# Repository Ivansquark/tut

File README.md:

Some examples for future fast remembering

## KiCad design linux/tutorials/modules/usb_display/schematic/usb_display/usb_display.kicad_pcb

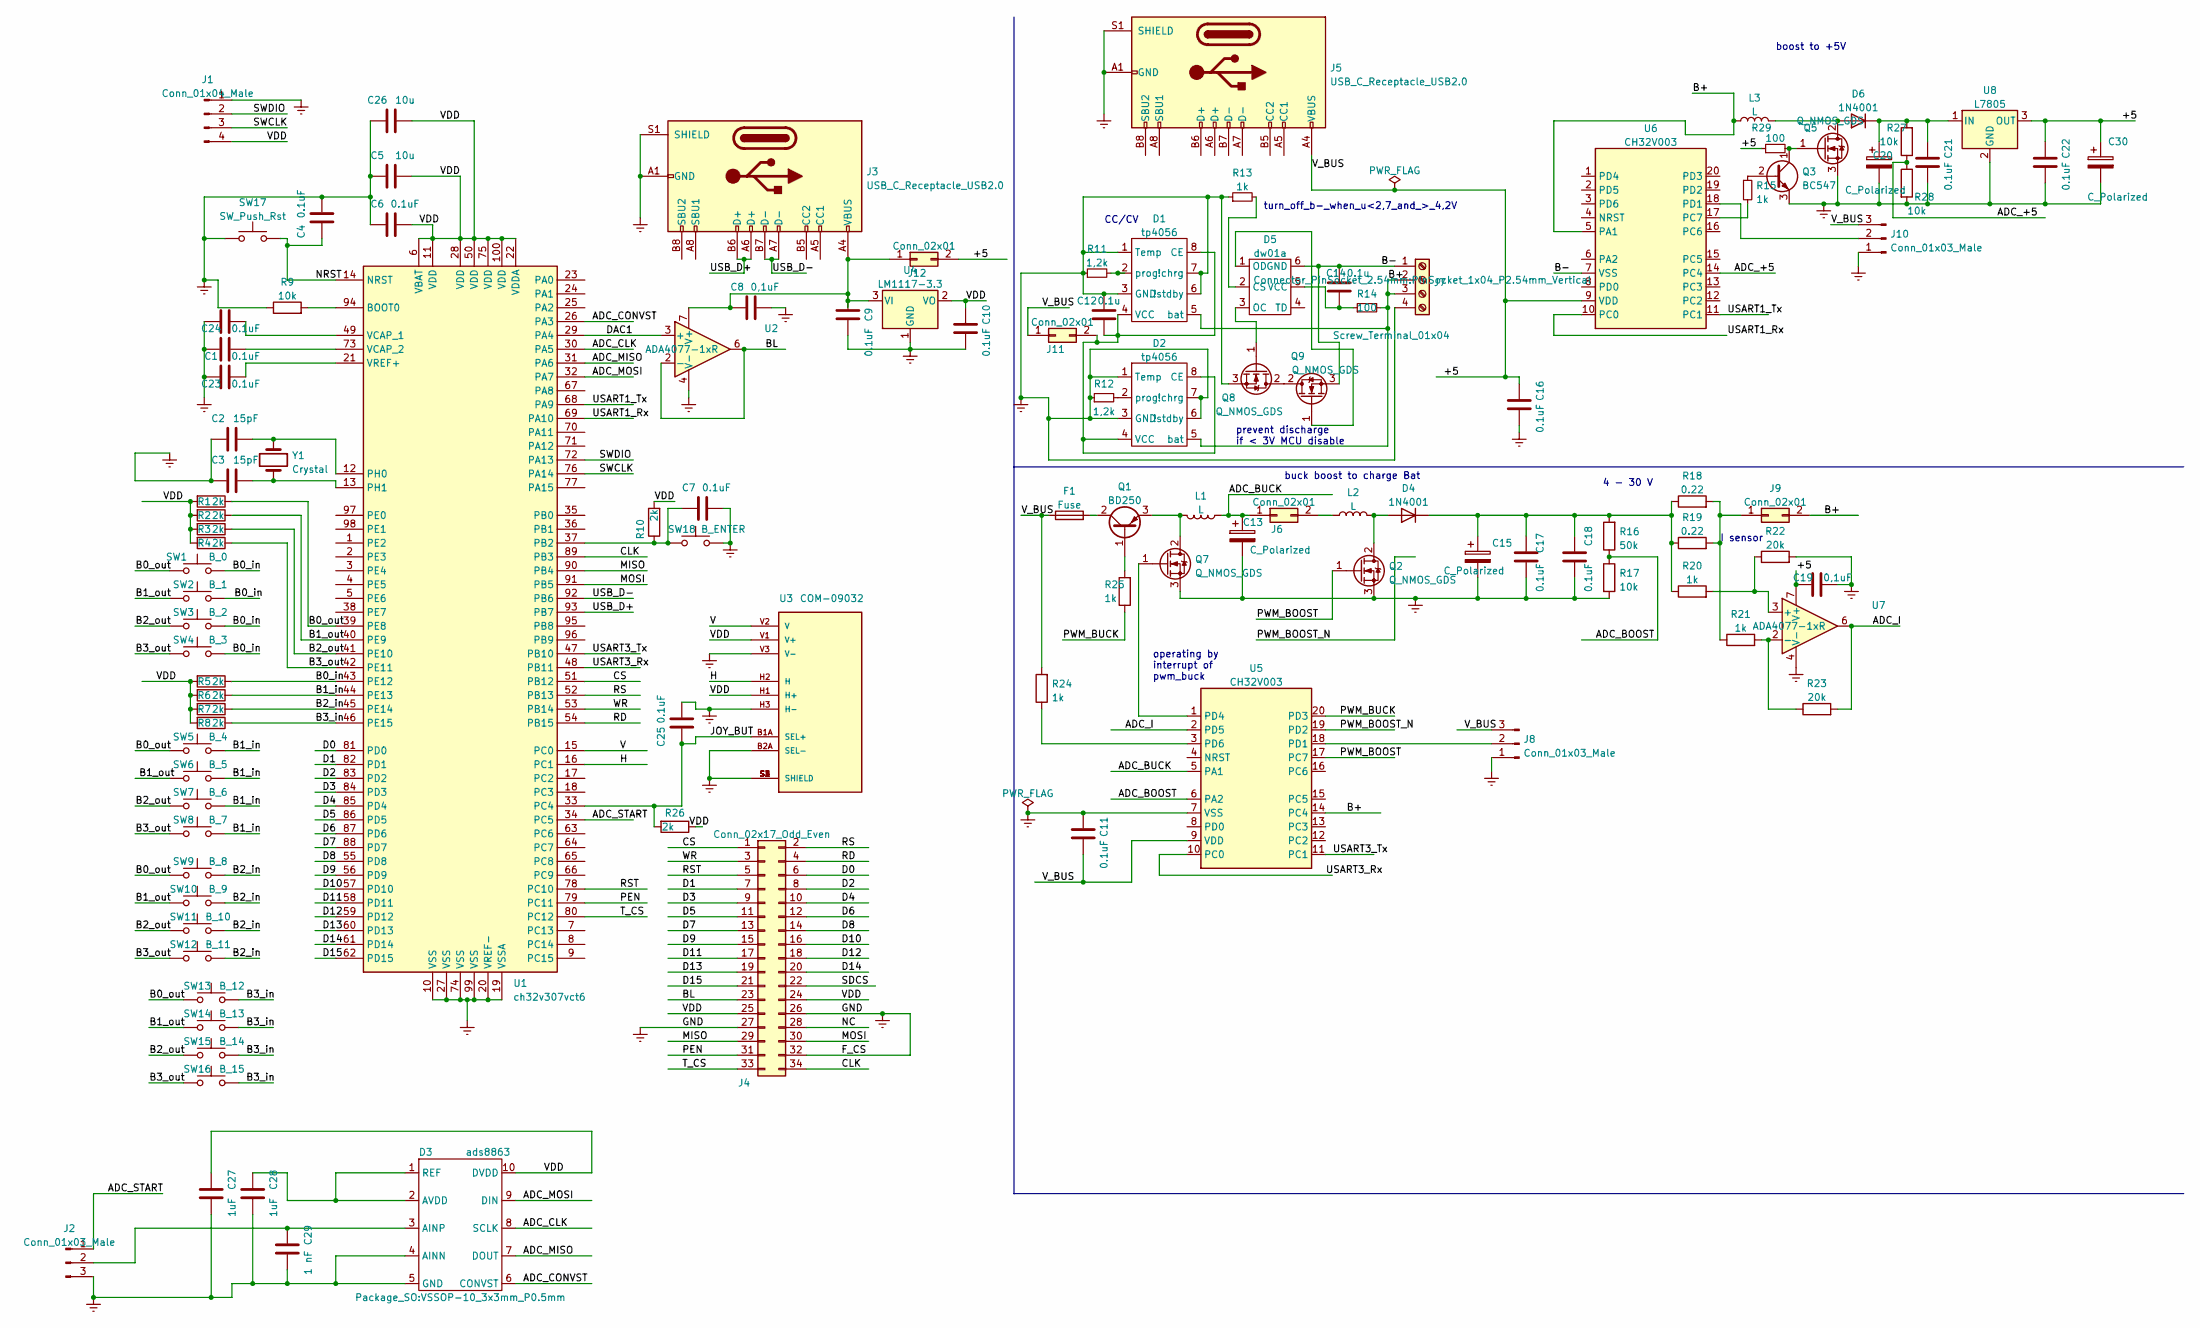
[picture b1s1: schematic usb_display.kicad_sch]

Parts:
C1, C4, C6, C7, C9, C10, C11, C16, C17, C18, C21, C22, C23, C24, C25: 0.1uF; C_0603_1608Metric
C2, C3: 15pF; C_0603_1608Metric
C5, C26: 10u; C_0603_1608Metric
C8, C19: 0,1uF; C_0603_1608Metric
C12, C14: 0.1u; C_0603_1608Metric
C13, C15, C20, C30: C_Polarized; CP_Radial_D8.0mm_P3.80mm
C27, C28: 1uF; C_0603_1608Metric
C29: 1 nF; C_0603_1608Metric
D1, D2: tp4056; SOIC-8_3.9x4.9mm_P1.27mm
D3: ads8863; VSSOP-10_3x3mm_P0.5mm
D4, D6: 1N4001; D_DO-41_SOD81_P10.16mm_Horizontal
D5: dw01a; TSOP-6_1.65x3.05mm_P0.95mm
F1: Fuse; Fuse_0603_1608Metric
J1: Conn_01x04_Male; PinHeader_1x04_P2.54mm_Vertical
J2, J8, J10: Conn_01x03_Male; PinHeader_1x03_P2.54mm_Vertical
J3, J5: USB_C_Receptacle_USB2.0; USB_C_Receptacle_HRO_TYPE-C-31-M-12
J4: Conn_02x17_Odd_Even; PinHeader_2x17_P2.54mm_Vertical
J6, J9, J11, J12: Conn_02x01; PinHeader_1x02_P2.54mm_Vertical
J7: Screw_Terminal_01x04; PinSocket_1x04_P2.54mm_Vertical
L1, L2, L3: L; L_Axial_L20.0mm_D8.0mm_P7.62mm_Vertical
Q1: BD250; TO-252-2
Q2, Q5, Q7, Q8, Q9: Q_NMOS_GDS; SOT-223
Q3: BC547; TO-92_Inline
R1, R2, R3, R4, R5, R6, R7, R8, R10, R26: 2k; R_0603_1608Metric
R9, R17, R27, R28: 10k; R_0603_1608Metric
R11, R12: 1,2k; R_0603_1608Metric
R13, R15, R20, R21, R24, R25: 1k; R_0603_1608Metric
R14, R29: 100; R_0603_1608Metric
R16: 50k; R_0603_1608Metric
R18, R19: 0.22; R_0603_1608Metric
R22, R23: 20k; R_0603_1608Metric
SW1: B_0; SW_PUSH_6mm_H8mm
SW2: B_1; SW_PUSH_6mm_H8mm
SW3: B_2; SW_PUSH_6mm_H8mm
SW4: B_3; SW_PUSH_6mm_H8mm
SW5: B_4; SW_PUSH_6mm_H8mm
SW6: B_5; SW_PUSH_6mm_H8mm
SW7: B_6; SW_PUSH_6mm_H8mm
SW8: B_7; SW_PUSH_6mm_H8mm
SW9: B_8; SW_PUSH_6mm_H8mm
SW10: B_9; SW_PUSH_6mm_H8mm
SW11: B_10; SW_PUSH_6mm_H8mm
SW12: B_11; SW_PUSH_6mm_H8mm
SW13: B_12; SW_PUSH_6mm_H8mm
SW14: B_13; SW_PUSH_6mm_H8mm
SW15: B_14; SW_PUSH_6mm_H8mm
SW16: B_15; SW_PUSH_6mm_H8mm
SW17: SW_Push_Rst; SW_PUSH_6mm_H8mm
SW18: B_ENTER; SW_PUSH_6mm_H8mm
U1: ch32v307vct6; LQFP-100_14x14mm_P0.5mm
U2, U7: ADA4077-1xR; SOIC-8_3.9x4.9mm_P1.27mm
U3: COM-09032; PS4_joystick; PARTREV N/A
U4: LM1117-3.3; SOT-223
U5, U6: CH32V003; TSSOP-20_4.4x6.5mm_P0.65mm
U8: L7805; TO-252-2
Y1: Crystal; Crystal_HC18-U_Vertical

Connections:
/+5: C11.1, C16.2, C19.2, C22.2, C30.1, F1.1, J5.A4 (VBUS), J5.A9 (VBUS), J5.B4 (VBUS), J5.B9 (VBUS), J8.3, J10.3, J11.1, J12.2, R24.2, R29.1, U5.9 (VDD), U6.9 (VDD), U7.7 (V+), U8.3 (OUT)
/ADC_+5: R27.1, R28.1, U6.14 (PC4)
/ADC_BOOST: R16.1, R17.1, U5.6 (PA2)
/ADC_BUCK: C13.1, J6.1, L1.1, U5.5 (PA1)
/ADC_CLK: D3.8 (SCLK), U1.30 (PA5)
/ADC_CONVST: D3.6 (CONVST), U1.26 (PA3)
/ADC_I: R23.2, U5.2 (PD5), U7.6
/ADC_MISO: D3.7 (DOUT), U1.31 (PA6)
/ADC_MOSI: D3.9 (DIN), U1.32 (PA7)
/ADC_START: J2.1, U1.34 (PC5)
/B0_in: R5.1, SW1.2, SW2.2, SW3.2, SW4.2, U1.43 (PE12)
/B0_out: R1.1, SW1.1, SW5.1, SW9.1, SW13.1, U1.39 (PE8)
/B1_in: R6.1, SW5.2, SW6.2, SW7.2, SW8.2, U1.44 (PE13)
/B1_out: R2.1, SW2.1, SW6.1, SW10.1, SW14.1, U1.40 (PE9)
/B2_in: R7.1, SW9.2, SW10.2, SW11.2, SW12.2, U1.45 (PE14)
/B2_out: R3.1, SW3.1, SW7.1, SW11.1, SW15.1, U1.41 (PE10)
/B3_in: R8.1, SW13.2, SW14.2, SW15.2, SW16.2, U1.46 (PE15)
/B3_out: R4.1, SW4.1, SW8.1, SW12.1, SW16.1, U1.42 (PE11)
/B+: D1.5 (bat), D2.5 (bat), J7.2, J7.3, J9.2, L3.1, R14.2, U5.14 (PC4), U6.5 (PA1)
/B-: C14.1, D5.6 (GND), J7.1, Q9.3 (S), U6.7 (VSS)
/BL: J4.23, U2.2 (-), U2.6
/CLK: J4.34, U1.89 (PB3)
/CS: J4.1, U1.51 (PB12)
/D0: J4.6, U1.81 (PD0)
/D1: J4.7, U1.82 (PD1)
/D2: J4.8, U1.83 (PD2)
/D3: J4.9, U1.84 (PD3)
/D4: J4.10, U1.85 (PD4)
/D5: J4.11, U1.86 (PD5)
/D6: J4.12, U1.87 (PD6)
/D7: J4.13, U1.88 (PD7)
/D8: J4.14, U1.55 (PD8)
/D9: J4.15, U1.56 (PD9)
/D10: J4.16, U1.57 (PD10)
/D11: J4.17, U1.58 (PD11)
/D12: J4.18, U1.59 (PD12)
/D13: J4.19, U1.60 (PD13)
/D14: J4.20, U1.61 (PD14)
/D15: J4.21, U1.62 (PD15)
/DAC1: U1.29 (PA4), U2.3 (+)
/H: U1.16 (PC1), U3.H2 (H)
/JOY_BUT: C25.2, R26.2, U1.33 (PC4), U3.B1A (SEL+)
/MISO: J4.29, U1.90 (PB4)
/MOSI: J4.30, U1.91 (PB5)
/NC: J4.28
/NRST: C4.2, SW17.2, U1.14 (NRST)
/PEN: J4.31, U1.79 (PC11)
/PWM_BOOST: Q2.1 (G), U5.17 (PC7)
/PWM_BOOST_N: U5.19 (PD2)
/PWM_BUCK: R25.1, U5.20 (PD3)
/RD: J4.4, U1.54 (PB15)
/RS: J4.2, U1.52 (PB13)
/RST: J4.5, U1.78 (PC10)
/SDCS: J4.22
/SWCLK: J1.3, U1.76 (PA14)
/SWDIO: J1.2, U1.72 (PA13)
/T_CS: J4.33, U1.80 (PC12)
/USART1_Rx: U1.69 (PA10), U6.10 (PC0)
/USART1_Tx: U1.68 (PA9), U6.11 (PC1)
/USART3_Rx: U1.48 (PB11), U5.10 (PC0)
/USART3_Tx: U1.47 (PB10), U5.11 (PC1)
/USB_D+: J3.A6 (D+), J3.B6 (D+), U1.93 (PB7)
/USB_D-: J3.A7 (D-), J3.B7 (D-), U1.92 (PB6)
/V: U1.15 (PC0), U3.V2 (V)
/VDD: C5.1, C6.1, C10.2, C26.1, C27.2, D3.10 (DVDD), J1.4, J4.24, J4.25, R1.2, R2.2, R3.2, R4.2, R5.2, R6.2, R7.2, R8.2, R10.2, U1.6 (VBAT), U1.11 (VDD), U1.22 (VDDA), U1.28 (VDD), U1.50 (VDD), U1.75 (VDD), U1.100 (VDD), U3.H1 (H+), U3.V1 (V+), U4.2 (VO)
/WR: J4.3, U1.53 (PB14)
Earth: C1.2, C2.2, C3.2, C4.1, C5.2, C6.2, C7.1, C8.1, C9.1, C10.1, C11.2, C12.1, C13.2, C15.2, C16.1, C17.1, C18.1, C19.1, C20.2, C21.1, C22.1, C23.2, C24.2, C25.1, C26.2, C27.1, C28.1, C29.1, C30.2, D1.1 (Temp), D1.3 (GND), D1.6 (!stdby), D1.7 (!chrg), D2.1 (Temp), D2.3 (GND), D2.6 (!stdby), D2.7 (!chrg), D3.4 (AINN), D3.5 (GND), J1.1, J2.3, J3.A1 (GND), J3.A12 (GND), J3.B1 (GND), J3.B12 (GND), J3.S1 (SHIELD), J4.26, J4.27, J4.32, J5.A1 (GND), J5.A12 (GND), J5.B1 (GND), J5.B12 (GND), J5.S1 (SHIELD), J7.4, J8.1, J10.1, Q2.3 (S), Q3.3 (E), Q5.3 (S), Q7.3 (S), Q8.3 (S), R9.1, R11.1, R12.1, R13.1, R17.2, R22.2, R28.2, SW17.1, SW18.2, U1.10 (VSS), U1.19 (VSSA), U1.20 (VREF-), U1.27 (VSS), U1.74 (VSS), U1.99 (VSS), U2.4 (V-), U3.B2A (SEL-), U3.H3 (H-), U3.S1 (SHIELD), U3.S2 (SHIELD), U3.S3 (SHIELD), U3.S4 (SHIELD), U3.V3 (V-), U4.1 (GND), U5.7 (VSS), U7.4 (V-), U8.2 (GND)
unnamed: C1.1, U1.73 (VCAP_2)
unnamed: C2.1, U1.12 (PH0), Y1.1
unnamed: C3.1, U1.13 (PH1), Y1.2
unnamed: C7.2, R10.1, SW18.1, U1.37 (PB2)
unnamed: C8.2, C9.2, J3.A4 (VBUS), J3.A9 (VBUS), J3.B4 (VBUS), J3.B9 (VBUS), J12.1, U2.7 (V+), U4.3 (VI)
unnamed: C12.2, D1.4 (VCC), D1.8 (CE), D2.4 (VCC), D2.8 (CE), J11.2
unnamed: C14.2, D5.5 (VCC), R14.1
unnamed: C15.1, C17.2, C18.2, D4.1 (K), R16.2, R18.1, R19.1, R20.1
unnamed: C20.1, C21.2, D6.1 (K), R27.2, U8.1 (IN)
unnamed: C23.1, U1.21 (VREF+)
unnamed: C24.1, U1.49 (VCAP_1)
unnamed: C28.2, D3.1 (REF), D3.2 (AVDD)
unnamed: C29.2, D3.3 (AINP), J2.2
unnamed: D1.2 (prog), R11.2
unnamed: D2.2 (prog), R12.2
unnamed: D4.2 (A), L2.2, Q2.2 (D)
unnamed: D5.1 (OD), Q9.1 (G)
unnamed: D5.2 (CS), R13.2
unnamed: D5.3 (OC), Q8.1 (G)
unnamed: D6.2 (A), L3.2, Q5.2 (D)
unnamed: F1.2, Q1.2 (C)
unnamed: J6.2, L2.1
unnamed: J8.2, U5.18 (PD1)
unnamed: J9.1, R18.2, R19.2, R21.1
unnamed: J10.2, U6.18 (PD1)
unnamed: L1.2, Q1.3 (E), Q7.2 (D)
unnamed: Q1.1 (B), R25.2
unnamed: Q3.2 (B), R15.1
unnamed: Q3.1 (C), Q5.1 (G), R29.2
unnamed: Q7.1 (G), U5.1 (PD4)
unnamed: Q8.2 (D), Q8.4, Q9.2 (D), Q9.4
unnamed: R9.2, U1.94 (BOOT0)
unnamed: R20.2, R22.1, U7.3 (+)
unnamed: R21.2, R23.1, U7.2 (-)
unnamed: R24.1, U5.3 (PD6)
unnamed: R15.2, U6.17 (PC7)

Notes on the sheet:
4 - 30 V
turn_off_b-_when_u<2,7_and_>_4,2V
CC/CV
I sensor
prevent discharge if < 3V MCU disable
operating by interrupt of pwm_buck
buck boost to charge Bat
boost to +5V

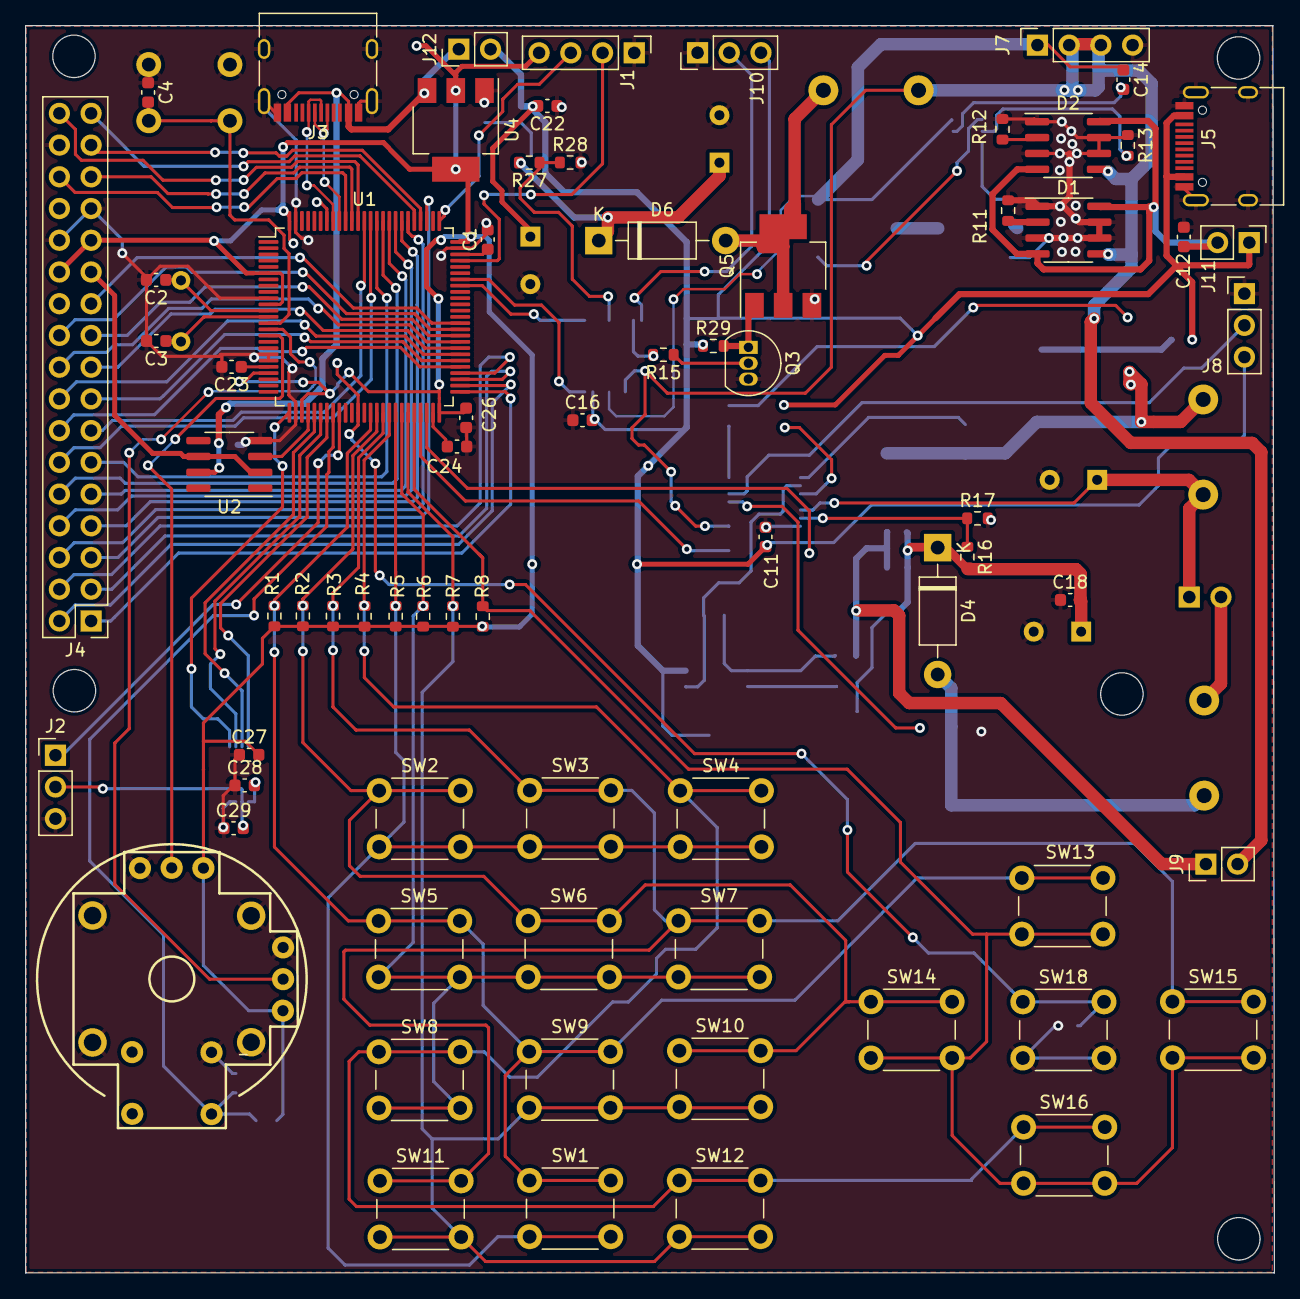
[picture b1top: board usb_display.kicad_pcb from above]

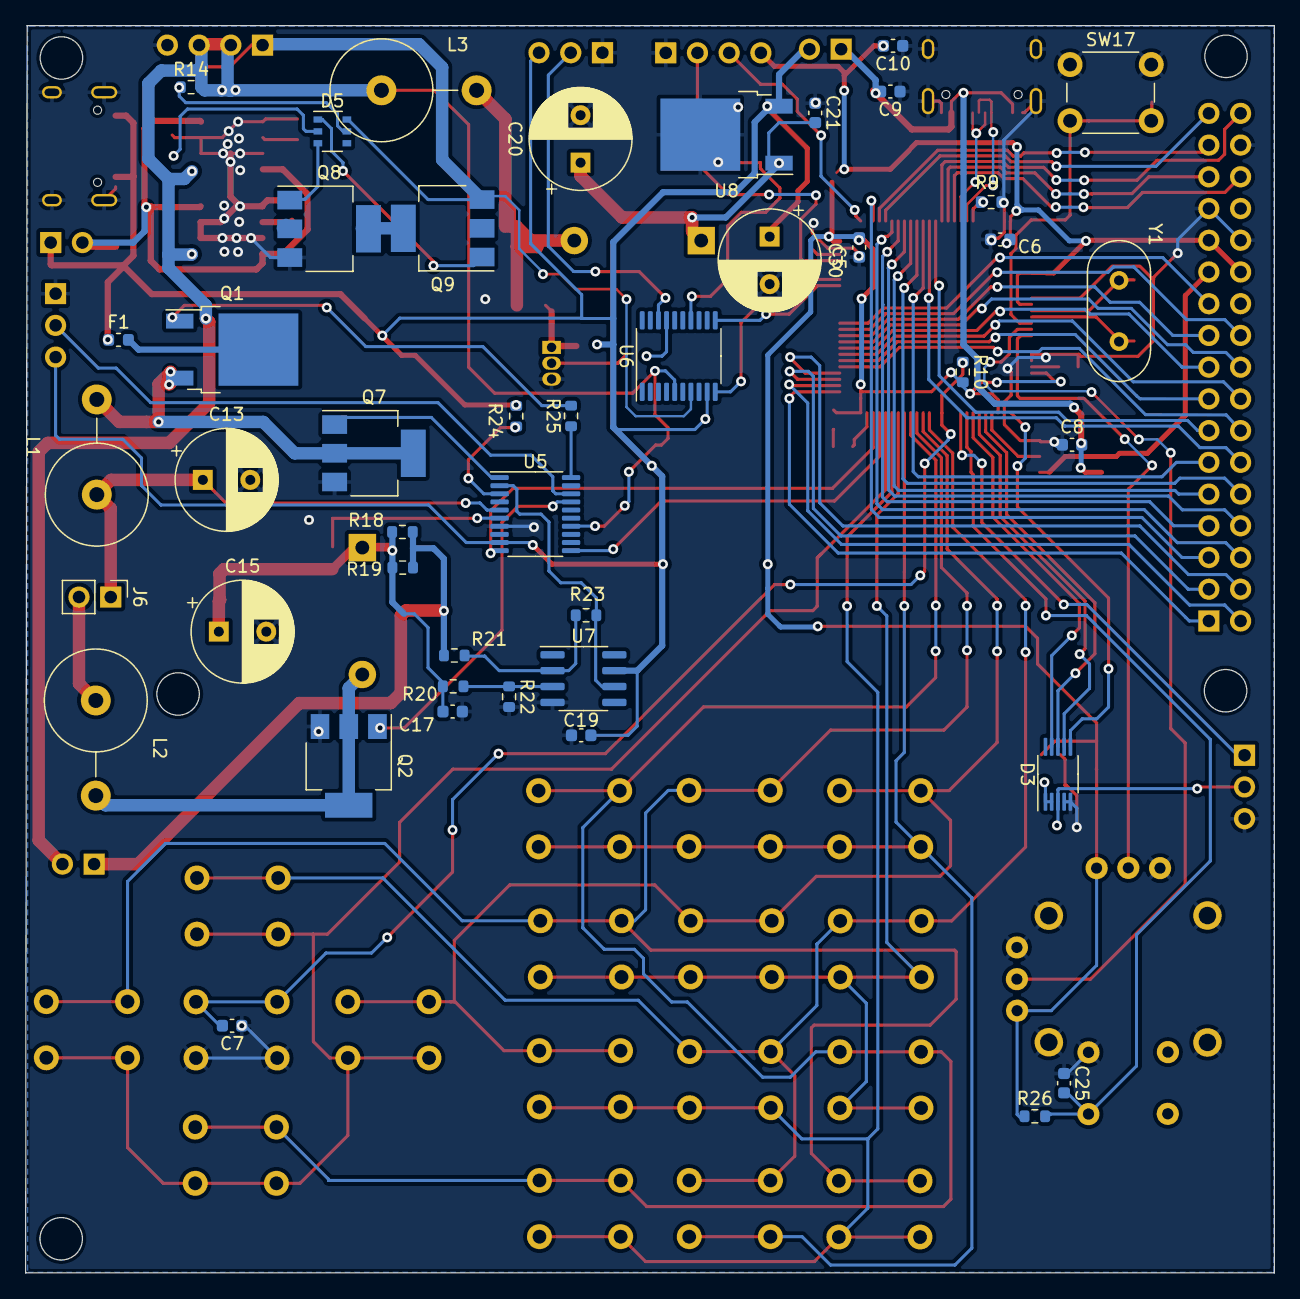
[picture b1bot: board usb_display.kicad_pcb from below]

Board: 2 copper layers, 100.0 x 99.9 mm, 115 parts (44 on the bottom side), 100 nets.

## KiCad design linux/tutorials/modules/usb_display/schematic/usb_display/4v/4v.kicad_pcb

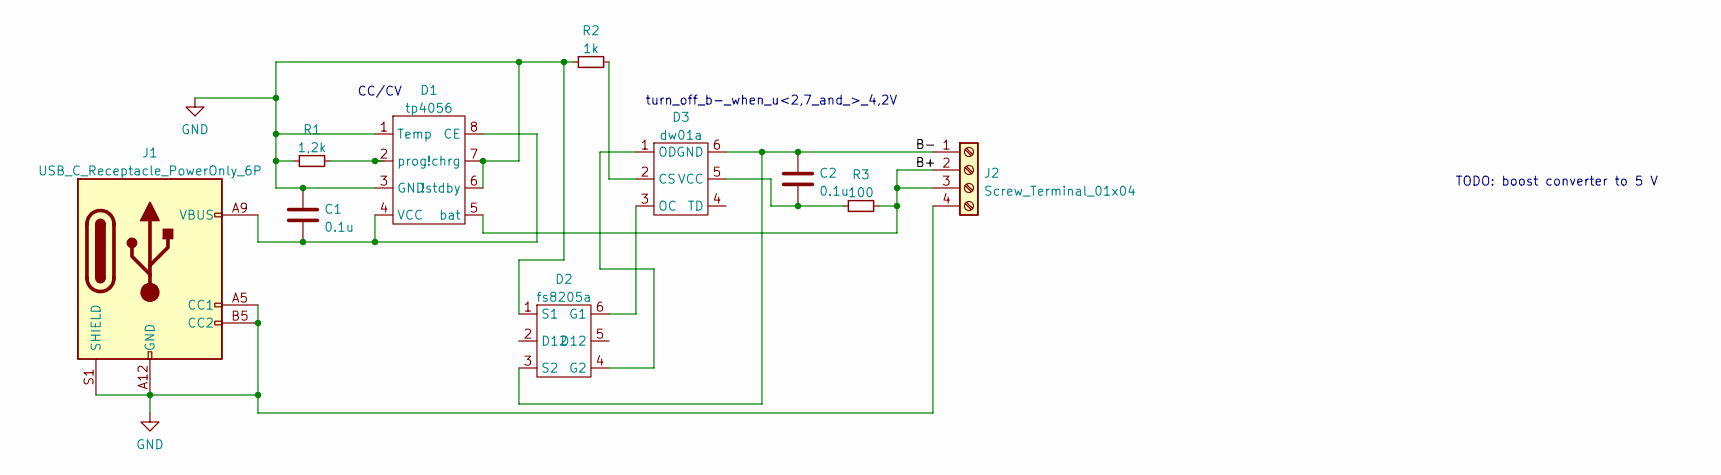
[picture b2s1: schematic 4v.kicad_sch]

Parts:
C1, C2: 0.1u; C_0603_1608Metric
D1: tp4056
D2: fs8205a; dw01a
D3: dw01a
J1: USB_C_Receptacle_PowerOnly_6P; USB_C_Receptacle_HRO_TYPE-C-31-M-12
J2: Screw_Terminal_01x04; PinSocket_1x04_P2.00mm_Vertical
R1: 1,2k; R_0603_1608Metric
R2: 1k; R_0603_1608Metric
R3: 100; R_0603_1608Metric

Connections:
/B+: D1.5 (bat), J2.2, J2.3, R3.2
/B-: C2.1, D2.3 (S2), D3.6 (GND), J2.1
GND: C1.1, D1.1 (Temp), D1.3 (GND), D1.6 (!stdby), D1.7 (!chrg), D2.1 (S1), J1.A1, J1.A5 (CC1), J1.A12 (GND), J1.B1, J1.B5 (CC2), J1.B12 (GND), J1.S1 (SHIELD), J2.4, R1.1, R2.1
unnamed: C1.2, D1.4 (VCC), D1.8 (CE), J1.A4, J1.A9 (VBUS), J1.B4, J1.B9 (VBUS)
unnamed: C2.2, D3.5 (VCC), R3.1
unnamed: D1.2 (prog), R1.2
unnamed: D2.4 (G2), D3.1 (OD)
unnamed: D2.6 (G1), D3.3 (OC)
unnamed: D3.2 (CS), R2.2

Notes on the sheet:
CC/CV
turn_off_b-_when_u<2,7_and_>_4,2V
TODO: boost converter to 5 V

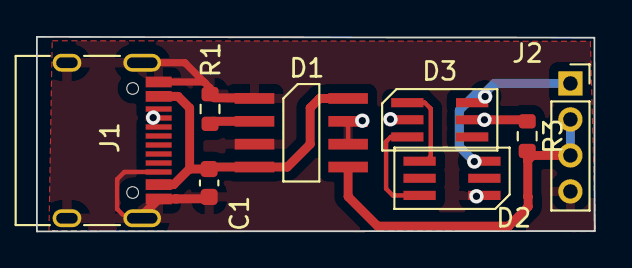
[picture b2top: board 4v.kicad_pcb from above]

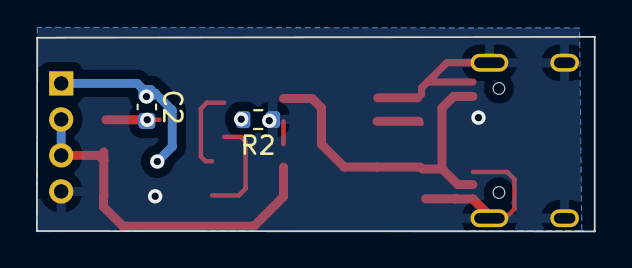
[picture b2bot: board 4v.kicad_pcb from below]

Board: 2 copper layers, 31.0 x 10.8 mm, 10 parts (2 on the bottom side), 9 nets.

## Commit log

2022-11-23 rebuild project
2022-11-23 add fonts
2022-11-23 test on riscv
2022-11-24 +program rotate
2023-06-05 +some tutorials
2023-08-24 + proj
2023-09-01 +usb display module (need to fix to write with own fb driver)
2023-09-05 usb display is worked on linux fb, but is needed to be fixed some bugs
2023-09-12 fix module to work with deferred_io_mmap to map user space on kernel space /dev/fb0
2023-09-15 need to implement file manager
2023-09-18 + console menu to start script
2023-09-19 +instruction of buildroot cmake package
2023-09-26 some new instructions
2023-10-04 consolemenu open file by name
2023-12-19 python
2023-12-19 add gtest
2023-12-19 from file
2023-12-20 +gtest from file
2023-12-21 add git instruction
2024-01-19 add test tut
2024-01-23 add short_allocator
2024-02-05 +ref
2024-03-01 emplace
2024-06-11 add some tests
2024-07-04 test laptop
2024-07-22 count secs
2024-11-10 lin_tut
2024-11-10 lin_tut1
2024-11-12 add shm
2024-11-12 sem start
2024-11-12 pipe
2024-11-13 fifo
2024-11-14 ccls
2024-11-16 file
2024-11-18 tcp/udp
2024-11-18 WIFSIGNALED NOT WORKING
2024-11-19 fix client
2024-11-19 format fixes
2024-11-19 some fix
2024-11-20 some fixes
2024-11-21 + merge list
2024-11-21 shmem mmap sem
2024-11-25 fix pipe
2024-11-27 xilinx
2024-11-28 instructions
2024-12-02 add instr for t113s4
2024-12-02 + kernel instr
2024-12-02 select
2024-12-03 instr uboot env to spi flash
2024-12-03 epoll level triggered
2024-12-04 add hush instr
2024-12-04 epoll nonblocked
2024-12-05 add FIT instruction
2024-12-05 my epoll
2024-12-06 add initramfs
2024-12-06 server getaddrinfo
2024-12-07 client
2024-12-08 server fork wait check
2024-12-08 server SIGCHILD from child
2024-12-10 wait
2024-12-10 wait add
2024-12-10 waitpid
2024-12-11 add instr
2024-12-12 daemon server start
2024-12-13 instr
2024-12-13 epoll client
2024-12-14 start write threadpool
2024-12-15 threadpool not work
2024-12-16 test threadpool
2024-12-16 serv
2024-12-17 fix cv
2024-12-17 cv in queue
2024-12-18 cv in threadpool
2024-12-18 strtok must be fixed
2024-12-19 need to fix sigpipe to sigign
2024-12-19 notify one problem
2024-12-20 fast server epoll problem
2024-12-23 sha1instr
2024-12-23 add uboot .ccls
2024-12-24 gtest
2024-12-25 start gtest queue
2024-12-26 gtest queue problem
2024-12-28 file utils
2024-12-29 reordering
2024-12-29 add mutex to all
2025-01-02 instr zynq
2025-01-03 add instr eth
2025-01-06 add uboot gdb instruction
2025-01-08 add zynq project template
2025-01-09 repair
2025-01-12 start create drivers
2025-01-14 add instruction to proper kernel and module build
2025-01-16 some additions
2025-01-19 modules
2025-01-20 some additions in modules code
2025-01-21 add some drivers templates
